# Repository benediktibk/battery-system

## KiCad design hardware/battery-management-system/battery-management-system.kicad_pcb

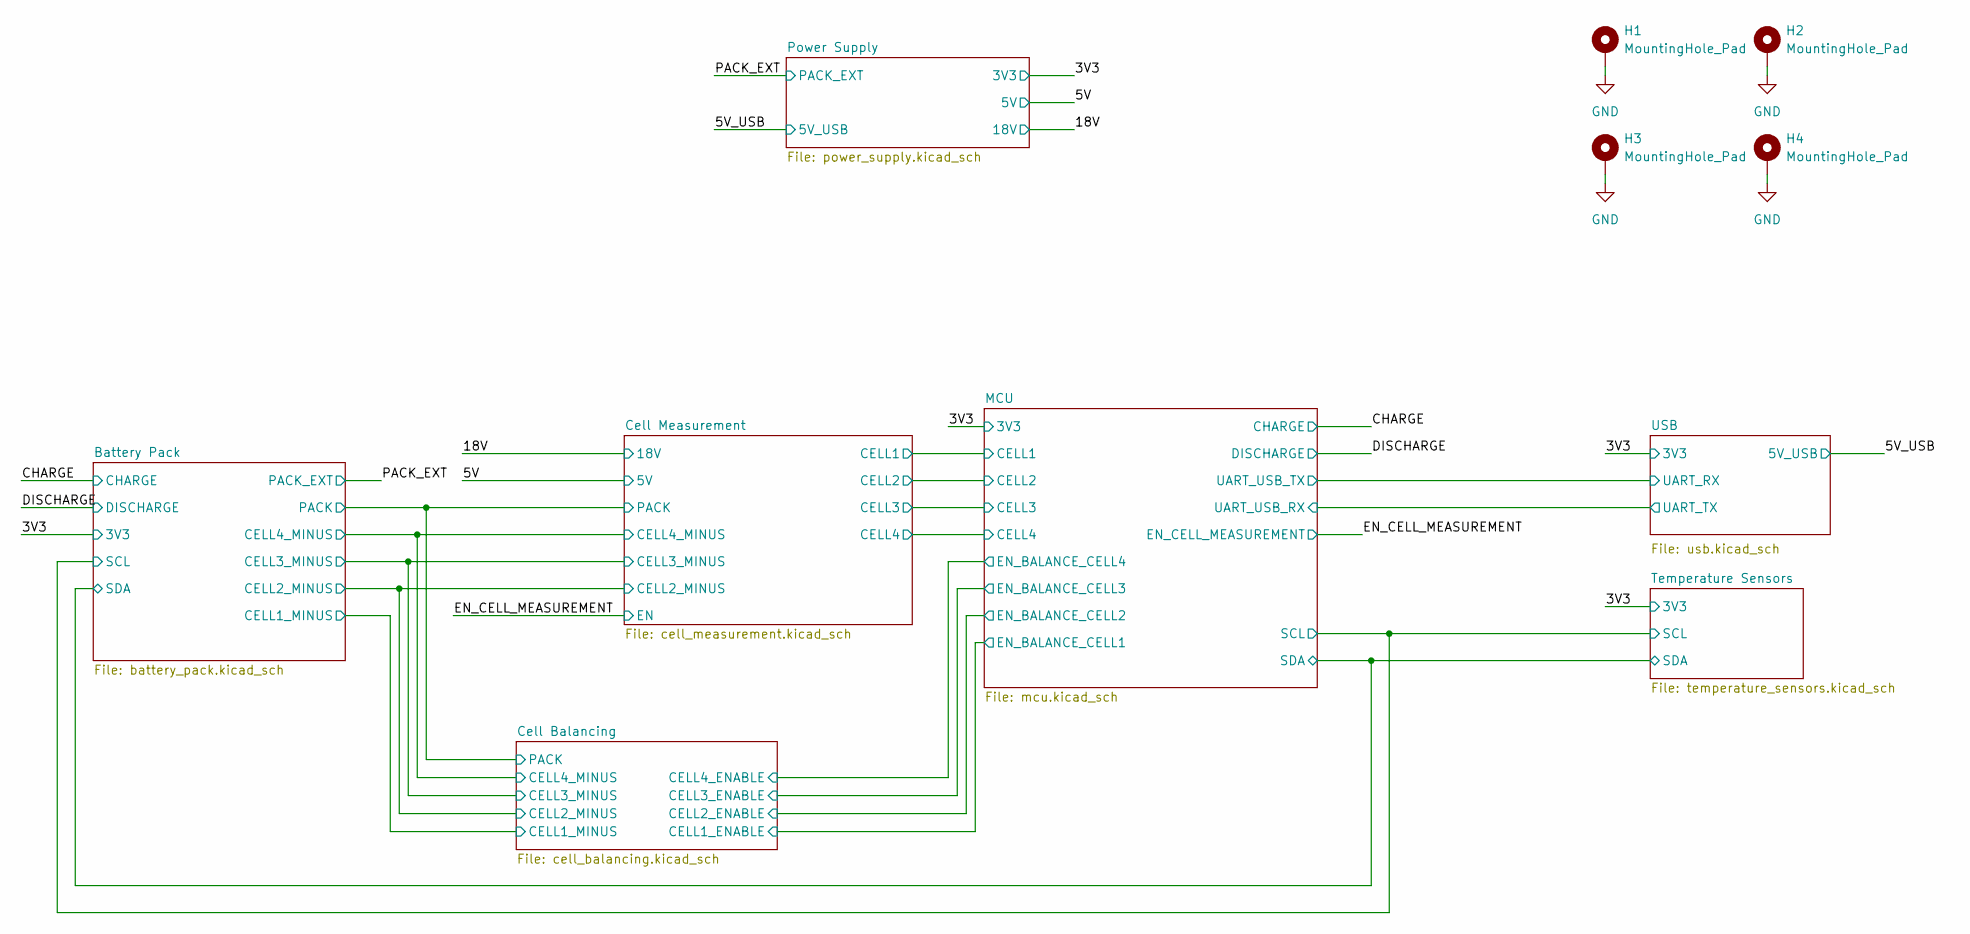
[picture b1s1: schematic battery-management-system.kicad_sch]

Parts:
H1, H2, H3, H4: MountingHole_Pad; MountingHole_6.4mm_M6_Pad_TopBottom

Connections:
GND: H1.1, H2.1, H3.1, H4.1; also elsewhere on the board

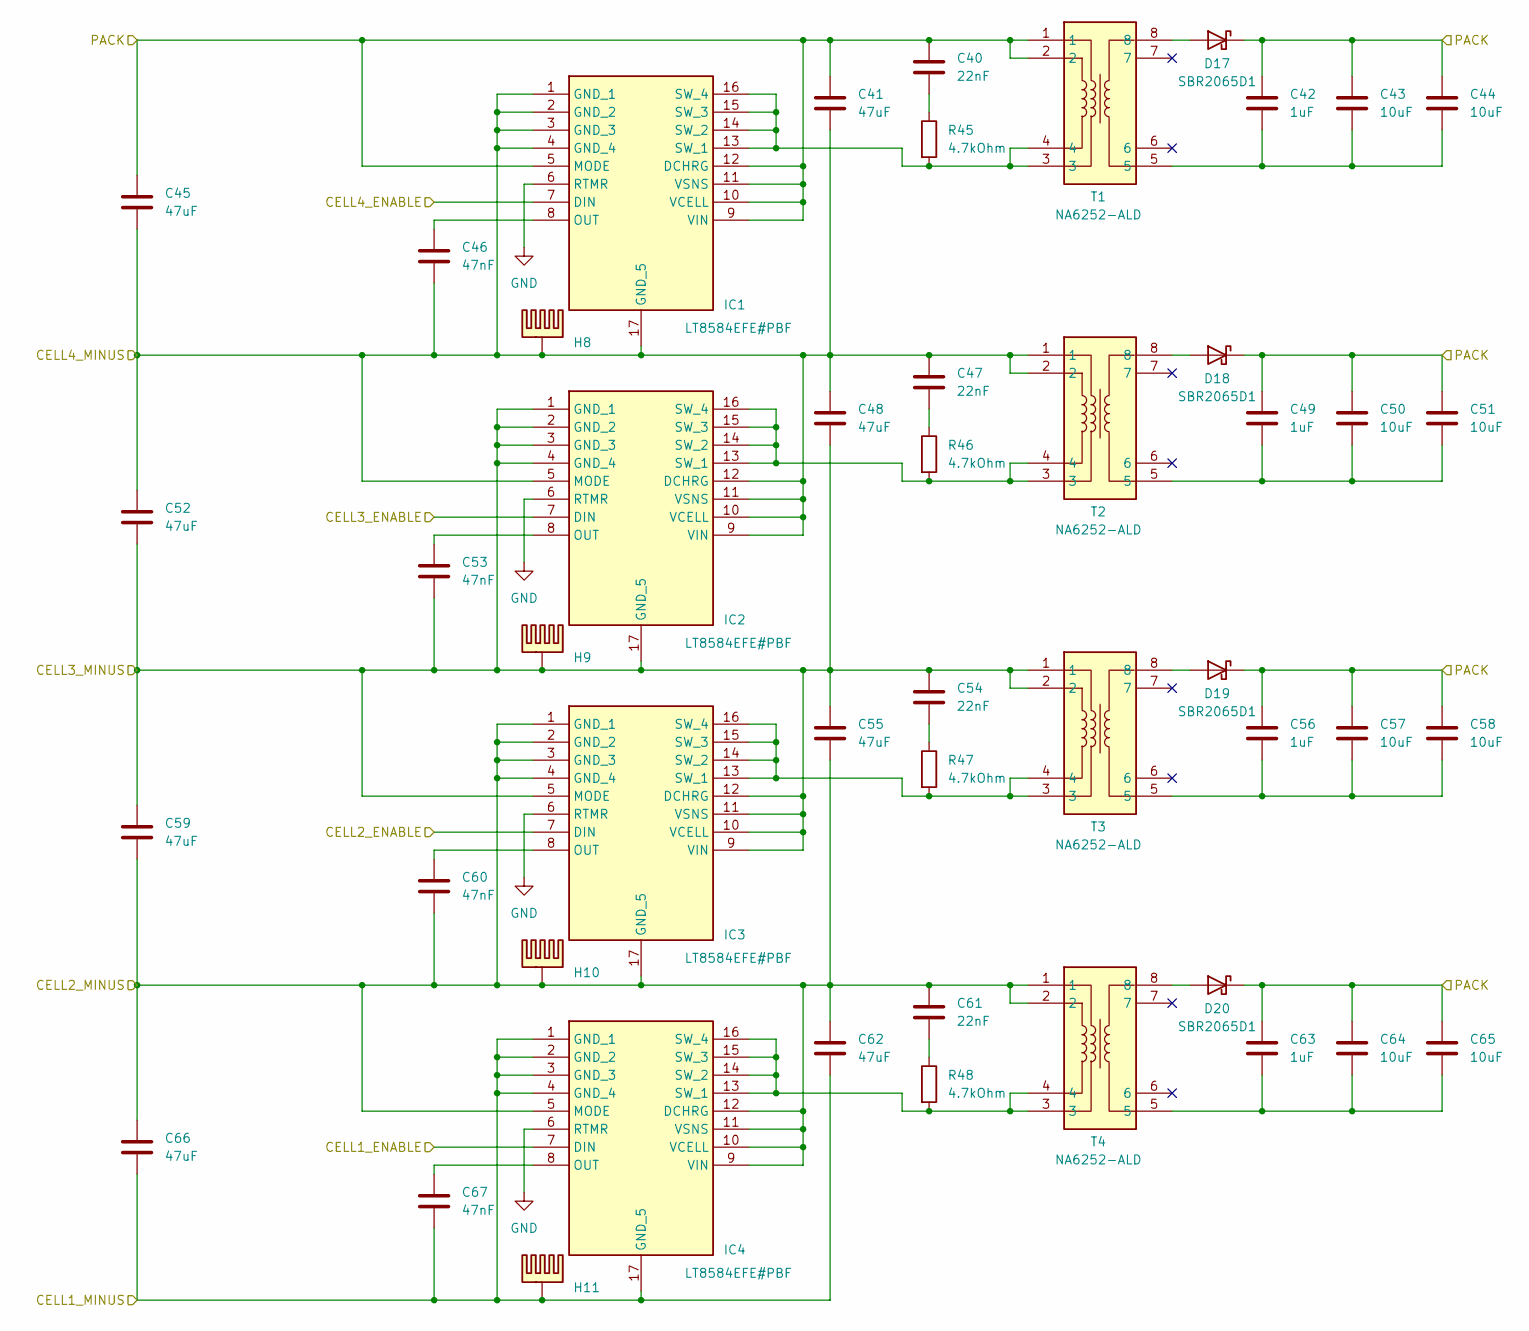
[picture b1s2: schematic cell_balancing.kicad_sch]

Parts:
C40, C47, C54, C61: 22nF; C_0603_1608Metric_Pad1.08x0.95mm_HandSolder; Mouser Part Number 80-C0603C223K4R
C41, C45, C48, C52, C55, C59, C62, C66: 47uF; C_1206_3216Metric_Pad1.33x1.80mm_HandSolder; Mouser Part Number 810-C3216X5R1E476M
C42, C49, C56, C63: 1uF; C_0603_1608Metric_Pad1.08x0.95mm_HandSolder; Mouser Part Number 963-UMK107BJ105KA-T
C43, C44, C50, C51, C57, C58, C64, C65: 10uF; C_1210_3225Metric_Pad1.33x2.70mm_HandSolder; Mouser Part Number 187-CL31A106MBHNNNE
C46, C53, C60, C67: 47nF; C_0603_1608Metric_Pad1.08x0.95mm_HandSolder; Mouser Part Number 80-C0603C473K4RACLR
D17, D18, D19, D20: SBR2065D1; Mouser Part Number 621-SBR2065D1-13
H8, H9, H10, H11: heatsink_18x18; Mouser Part Number 490-HSB06-181810; Mouser order number 490-HSB06-181810
IC1, IC2, IC3, IC4: LT8584EFE#PBF; SOP65P640X110-17N; Mouser Part Number 584-LT8584EFE#PBF; Mouser order number 584-LT8584EFE#PBF
R45, R46, R47, R48: 4.7kOhm; R_0603_1608Metric_Pad0.98x0.95mm_HandSolder; Mouser Part Number 652-CR0603FX-4701ELF
T1, T2, T3, T4: NA6252-ALD; SOP250P1524X1143-8N; Mouser Part Number 994-NA6252-ALD; Mouser order number 994-NA6252-ALD

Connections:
/Battery Pack/CELL1_MINUS: C62.2, C66.2, C67.2, H11.PAD, IC4.1 (GND_1), IC4.2 (GND_2), IC4.3 (GND_3), IC4.4 (GND_4), IC4.17 (GND_5); also elsewhere on the board
/Battery Pack/CELL2_MINUS: C55.2, C59.2, C60.2, C61.1, C62.1, C66.1, H10.PAD, IC3.1 (GND_1), IC3.2 (GND_2), IC3.3 (GND_3), IC3.4 (GND_4), IC3.17 (GND_5), IC4.5 (MODE), IC4.9 (VIN), IC4.10 (VCELL), IC4.11 (VSNS), IC4.12 (DCHRG), T4.1, T4.2; also elsewhere on the board
/Battery Pack/CELL3_MINUS: C48.2, C52.2, C53.2, C54.1, C55.1, C59.1, H9.PAD, IC2.1 (GND_1), IC2.2 (GND_2), IC2.3 (GND_3), IC2.4 (GND_4), IC2.17 (GND_5), IC3.5 (MODE), IC3.9 (VIN), IC3.10 (VCELL), IC3.11 (VSNS), IC3.12 (DCHRG), T3.1, T3.2; also elsewhere on the board
/Battery Pack/CELL4_MINUS: C41.2, C45.2, C46.2, C47.1, C48.1, C52.1, H8.PAD, IC1.1 (GND_1), IC1.2 (GND_2), IC1.3 (GND_3), IC1.4 (GND_4), IC1.17 (GND_5), IC2.5 (MODE), IC2.9 (VIN), IC2.10 (VCELL), IC2.11 (VSNS), IC2.12 (DCHRG), T2.1, T2.2; also elsewhere on the board
/Battery Pack/PACK: C40.1, C41.1, C42.1, C43.1, C44.1, C45.1, C49.1, C50.1, C51.1, C56.1, C57.1, C58.1, C63.1, C64.1, C65.1, D17.2 (K), D18.2 (K), D19.2 (K), D20.2 (K), IC1.5 (MODE), IC1.9 (VIN), IC1.10 (VCELL), IC1.11 (VSNS), IC1.12 (DCHRG), T1.1, T1.2; also elsewhere on the board
/Cell Balancing/CELL1_ENABLE: IC4.7 (DIN); also elsewhere on the board
/Cell Balancing/CELL2_ENABLE: IC3.7 (DIN); also elsewhere on the board
/Cell Balancing/CELL3_ENABLE: IC2.7 (DIN); also elsewhere on the board
/Cell Balancing/CELL4_ENABLE: IC1.7 (DIN); also elsewhere on the board
GND: IC1.6 (RTMR), IC2.6 (RTMR), IC3.6 (RTMR), IC4.6 (RTMR); also elsewhere on the board
unnamed: C40.2, R45.1
unnamed: C42.2, C43.2, C44.2, T1.5
unnamed: C47.2, R46.1
unnamed: C49.2, C50.2, C51.2, T2.5
unnamed: C54.2, R47.1
unnamed: C56.2, C57.2, C58.2, T3.5
unnamed: C61.2, R48.1
unnamed: C63.2, C64.2, C65.2, T4.5
unnamed: D17.1 (A), T1.8
unnamed: D18.1 (A), T2.8
unnamed: D19.1 (A), T3.8
unnamed: D20.1 (A), T4.8
unnamed: C46.1, IC1.8 (OUT)
unnamed: IC1.13 (SW_1), IC1.14 (SW_2), IC1.15 (SW_3), IC1.16 (SW_4), R45.2, T1.3, T1.4
unnamed: C53.1, IC2.8 (OUT)
unnamed: IC2.13 (SW_1), IC2.14 (SW_2), IC2.15 (SW_3), IC2.16 (SW_4), R46.2, T2.3, T2.4
unnamed: C60.1, IC3.8 (OUT)
unnamed: IC3.13 (SW_1), IC3.14 (SW_2), IC3.15 (SW_3), IC3.16 (SW_4), R47.2, T3.3, T3.4
unnamed: C67.1, IC4.8 (OUT)
unnamed: IC4.13 (SW_1), IC4.14 (SW_2), IC4.15 (SW_3), IC4.16 (SW_4), R48.2, T4.3, T4.4

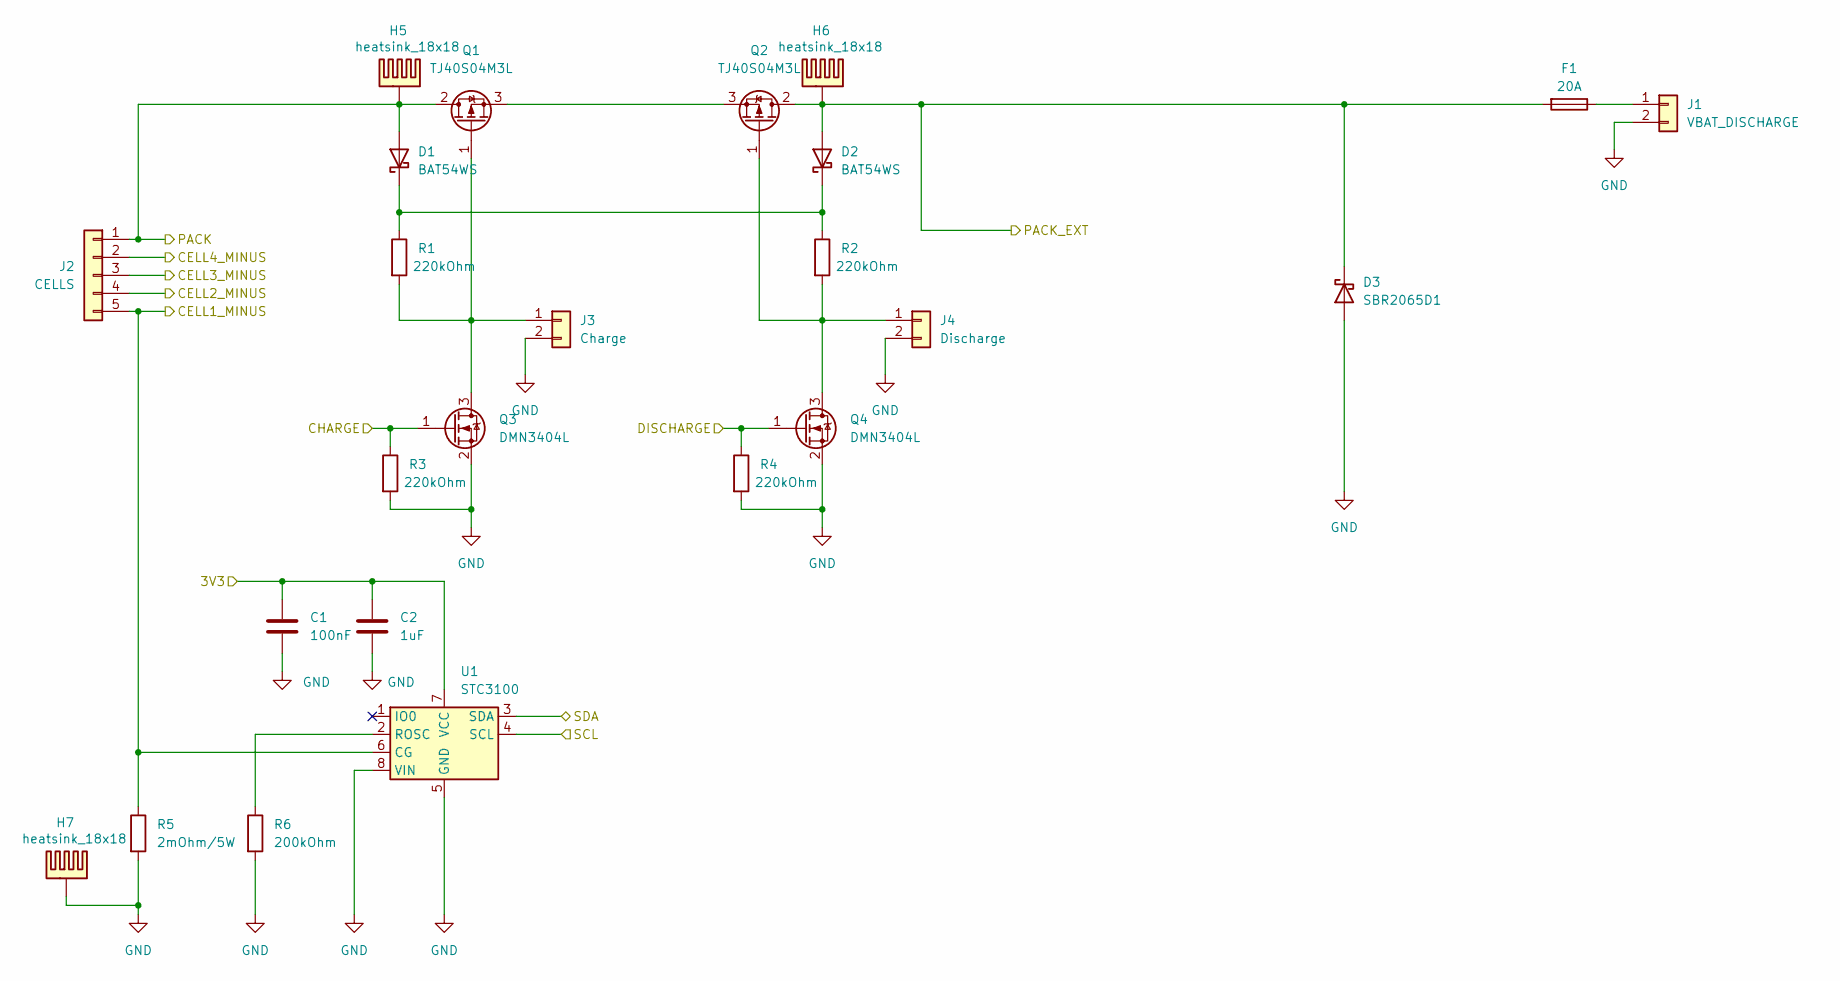
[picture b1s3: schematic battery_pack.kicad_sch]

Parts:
C1: 100nF; C_0603_1608Metric_Pad1.08x0.95mm_HandSolder; Mouser Part Number 581-KGM15BR71H104KM
C2: 1uF; C_0603_1608Metric_Pad1.08x0.95mm_HandSolder; Mouser Part Number 963-UMK107BJ105KA-T
D1, D2: BAT54WS; D_SOD-323; Mouser Part Number 637-BAT54WS
D3: SBR2065D1; Mouser Part Number 621-SBR2065D1-13
F1: 20A; KEYSTONE_blade_fus_holder
H5, H6, H7: heatsink_18x18; Mouser Part Number 490-HSB06-181810; Mouser order number 490-HSB06-181810
J1: VBAT_DISCHARGE; rspro_header_2pin_5_08mm
J2: CELLS; rspro_header_5pin_5_08mm
J3: Charge; PinHeader_1x02_P2.54mm_Vertical
J4: Discharge; PinHeader_1x02_P2.54mm_Vertical
Q1, Q2: TJ40S04M3L; TO-252-2; Mouser Part Number 757-TJ40S04M3LT6L1NQ
Q3, Q4: DMN3404L; SOT-23; Mouser Part Number 621-DMN3404L-7
R1, R2, R3, R4: 220kOhm; R_0603_1608Metric_Pad0.98x0.95mm_HandSolder; Mouser Part Number 71-CRCW0603-220K-E3
R5: 2mOhm/5W; R_2512_6332Metric_Pad1.40x3.35mm_HandSolder; Mouser Part Number 660-TLR3APSDTE2L00F7
R6: 200kOhm; R_0603_1608Metric_Pad0.98x0.95mm_HandSolder; Mouser Part Number 667-ERA-3AEB204V
U1: STC3100; MSOP-8_3x3mm_P0.65mm; Mouser Part Number 511-STC3100IST

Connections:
/3V3: C1.1, C2.1, U1.7 (VCC); also elsewhere on the board
/Battery Pack/CELL1_MINUS: J2.5, R5.1, U1.6 (CG); also elsewhere on the board
/Battery Pack/CELL2_MINUS: J2.4; also elsewhere on the board
/Battery Pack/CELL3_MINUS: J2.3; also elsewhere on the board
/Battery Pack/CELL4_MINUS: J2.2; also elsewhere on the board
/Battery Pack/PACK: D1.2 (A), H5.PAD, J2.1, Q1.2 (D); also elsewhere on the board
/CHARGE: Q3.1 (G), R3.1; also elsewhere on the board
/DISCHARGE: Q4.1 (G), R4.1; also elsewhere on the board
/MCU/SCL: U1.4 (SCL); also elsewhere on the board
/MCU/SDA: U1.3 (SDA); also elsewhere on the board
/PACK_EXT: D2.2 (A), D3.2 (K), F1.2, H6.PAD, Q2.2 (D); also elsewhere on the board
GND: C1.2, C2.2, D3.1 (A), H7.PAD, J1.2, J3.2, J4.2, Q3.2 (S), Q4.2 (S), R3.2, R4.2, R5.2, R6.2, U1.5 (GND), U1.8 (VIN); also elsewhere on the board
unnamed: D1.1 (K), D2.1 (K), R1.1, R2.1
unnamed: F1.1, J1.1
unnamed: J3.1, Q1.1 (G), Q3.3 (D), R1.2
unnamed: J4.1, Q2.1 (G), Q4.3 (D), R2.2
unnamed: Q1.3 (S), Q2.3 (S)
unnamed: R6.1, U1.2 (ROSC)

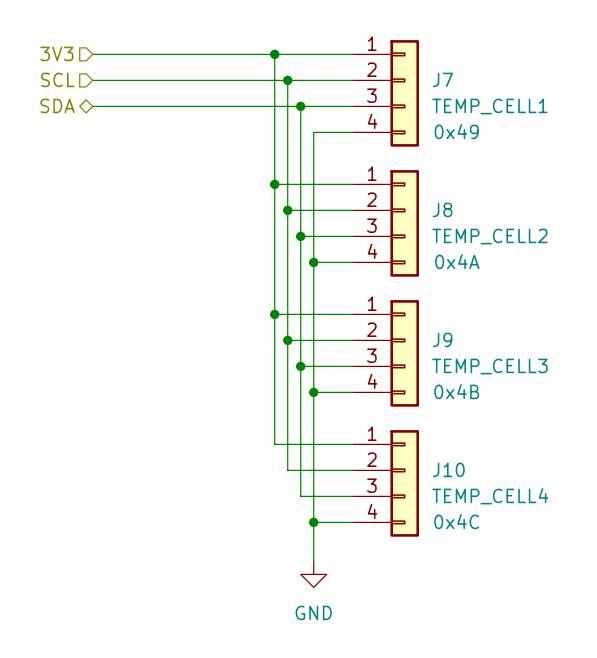
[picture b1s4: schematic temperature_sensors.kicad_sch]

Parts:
J7: TEMP_CELL1; rspro_header_4pin_3_5mm
J8: TEMP_CELL2; rspro_header_4pin_3_5mm
J9: TEMP_CELL3; rspro_header_4pin_3_5mm
J10: TEMP_CELL4; rspro_header_4pin_3_5mm

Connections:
/3V3: J7.1, J8.1, J9.1, J10.1; also elsewhere on the board
/MCU/SCL: J7.2, J8.2, J9.2, J10.2; also elsewhere on the board
/MCU/SDA: J7.3, J8.3, J9.3, J10.3; also elsewhere on the board
GND: J7.4, J8.4, J9.4, J10.4; also elsewhere on the board

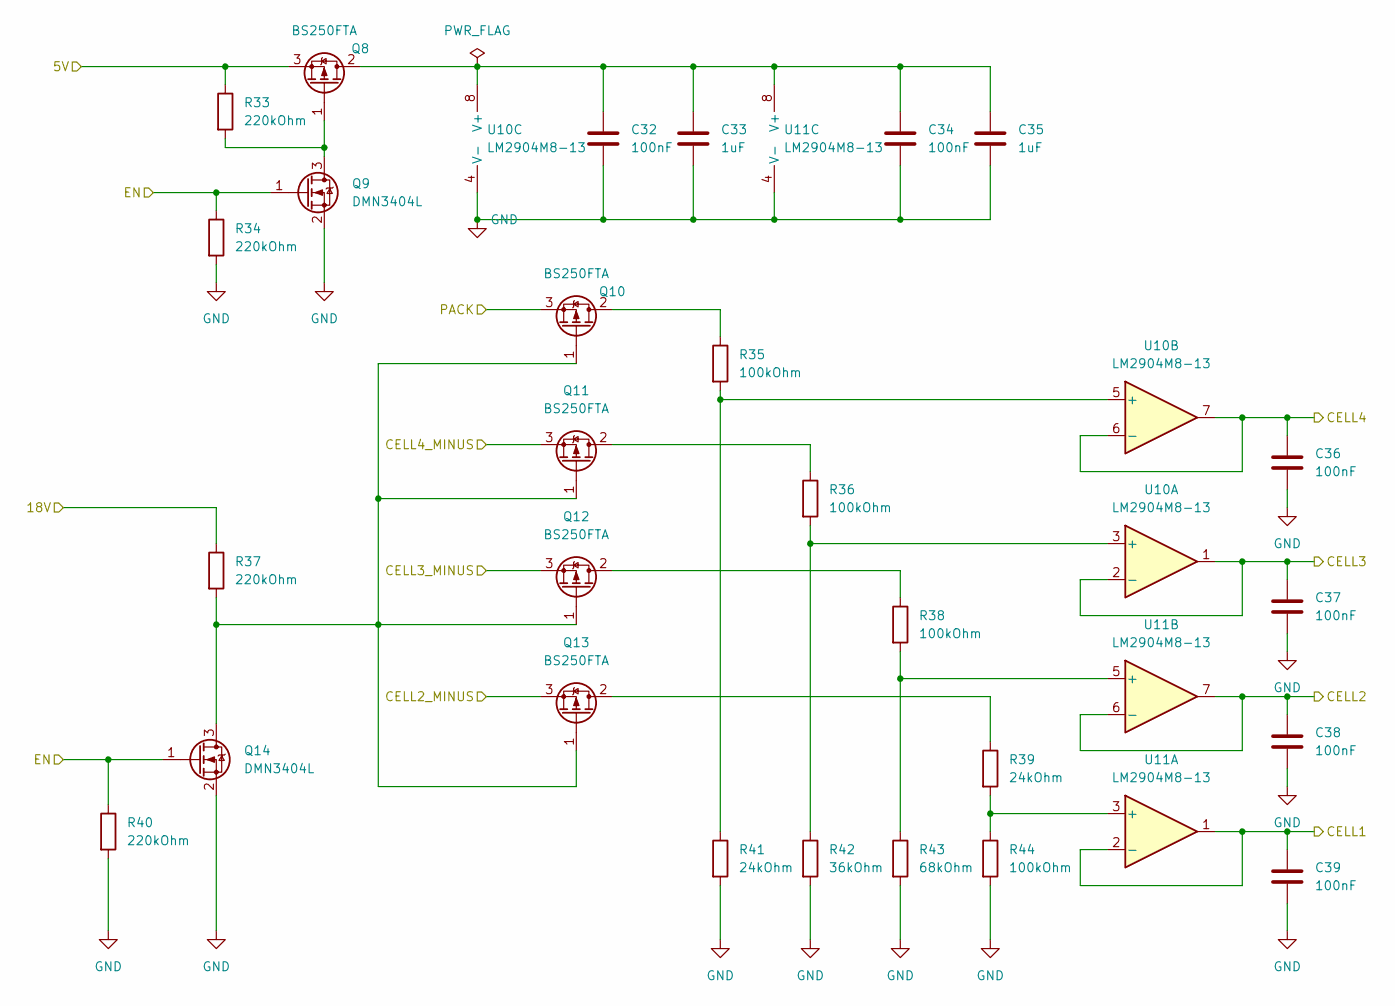
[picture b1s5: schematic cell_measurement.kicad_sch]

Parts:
C32, C34, C36, C37, C38, C39: 100nF; C_0603_1608Metric_Pad1.08x0.95mm_HandSolder; Mouser Part Number 581-KGM15BR71H104KM
C33, C35: 1uF; C_0603_1608Metric_Pad1.08x0.95mm_HandSolder; Mouser Part Number 963-UMK107BJ105KA-T
Q8, Q10, Q11, Q12, Q13: BS250FTA; SOT-23; Mouser Part Number 522-BS250FTA
Q9, Q14: DMN3404L; SOT-23; Mouser Part Number 621-DMN3404L-7
R33, R34, R37, R40: 220kOhm; R_0603_1608Metric_Pad0.98x0.95mm_HandSolder; Mouser Part Number 71-CRCW0603-220K-E3
R35, R36, R38, R44: 100kOhm; R_0603_1608Metric_Pad0.98x0.95mm_HandSolder; Mouser Part Number 603-RT0603FRE13100KL
R39, R41: 24kOhm; R_0603_1608Metric_Pad0.98x0.95mm_HandSolder; Mouser Part Number 71-CRCW060324K0FKEAC
R42: 36kOhm; R_0603_1608Metric_Pad0.98x0.95mm_HandSolder; Mouser Part Number 652-CR0603FX-3602ELF
R43: 68kOhm; R_0603_1608Metric_Pad0.98x0.95mm_HandSolder; Mouser Part Number 603-RT0603FRE0768KL
U10, U11: LM2904M8-13; MSOP-8_3x3mm_P0.65mm; Mouser Part Number 621-LM2904M8-13

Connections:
/5V: Q8.3 (S), R33.1; also elsewhere on the board
/18V: R37.1; also elsewhere on the board
/Battery Pack/CELL2_MINUS: Q13.3 (S); also elsewhere on the board
/Battery Pack/CELL3_MINUS: Q12.3 (S); also elsewhere on the board
/Battery Pack/CELL4_MINUS: Q11.3 (S); also elsewhere on the board
/Battery Pack/PACK: Q10.3 (S); also elsewhere on the board
/Cell Measurement/CELL1: C39.1, U11.1, U11.2 (-); also elsewhere on the board
/Cell Measurement/CELL2: C38.1, U11.6 (-), U11.7; also elsewhere on the board
/Cell Measurement/CELL3: C37.1, U10.1, U10.2 (-); also elsewhere on the board
/Cell Measurement/CELL4: C36.1, U10.6 (-), U10.7; also elsewhere on the board
/EN_CELL_MEASUREMENT: Q9.1 (G), Q14.1 (G), R34.1, R40.1; also elsewhere on the board
GND: C32.2, C33.2, C34.2, C35.2, C36.2, C37.2, C38.2, C39.2, Q9.2 (S), Q14.2 (S), R34.2, R40.2, R41.2, R42.2, R43.2, R44.2, U10.4 (V-), U11.4 (V-); also elsewhere on the board
unnamed: C32.1, C33.1, C34.1, C35.1, Q8.2 (D), U10.8 (V+), U11.8 (V+)
unnamed: Q8.1 (G), Q9.3 (D), R33.2
unnamed: Q10.2 (D), R35.1
unnamed: Q10.1 (G), Q11.1 (G), Q12.1 (G), Q13.1 (G), Q14.3 (D), R37.2
unnamed: Q11.2 (D), R36.1
unnamed: Q12.2 (D), R38.1
unnamed: Q13.2 (D), R39.1
unnamed: R36.2, R42.1, U10.3 (+)
unnamed: R35.2, R41.1, U10.5 (+)
unnamed: R39.2, R44.1, U11.3 (+)
unnamed: R38.2, R43.1, U11.5 (+)

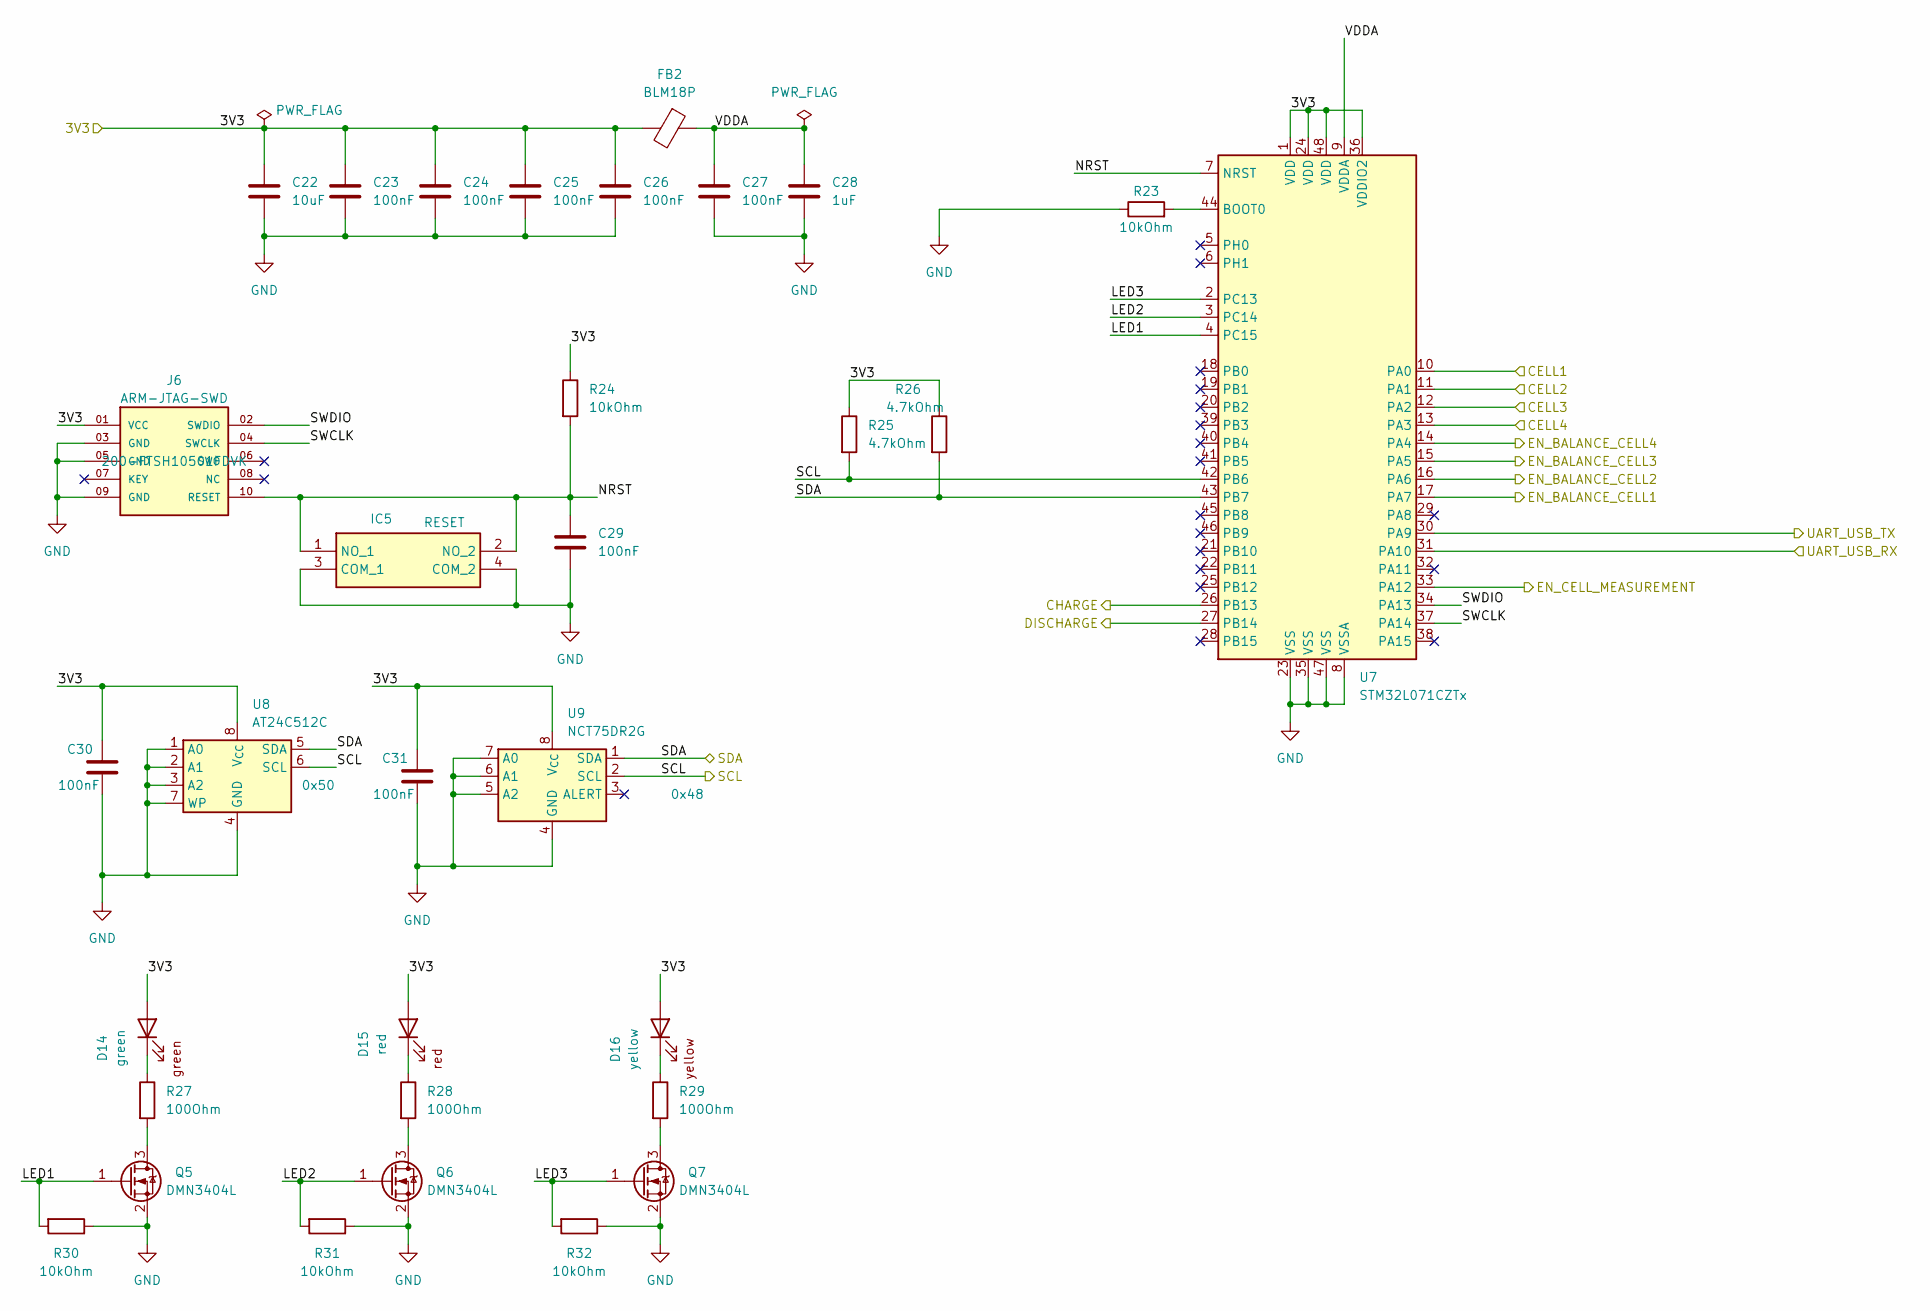
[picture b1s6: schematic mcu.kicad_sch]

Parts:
C22: 10uF; C_1210_3225Metric_Pad1.33x2.70mm_HandSolder; Mouser Part Number 187-CL31A106MBHNNNE
C23, C24, C25, C26, C27, C29, C30, C31: 100nF; C_0603_1608Metric_Pad1.08x0.95mm_HandSolder; Mouser Part Number 581-KGM15BR71H104KM
C28: 1uF; C_0603_1608Metric_Pad1.08x0.95mm_HandSolder; Mouser Part Number 963-UMK107BJ105KA-T
D14: green; D_0603_1608Metric_Pad1.05x0.95mm_HandSolder; Mouser Part Number 604-AP1608SGC
D15: red; D_0603_1608Metric_Pad1.05x0.95mm_HandSolder; Mouser Part Number 859-LTST-C190KDKT10A
D16: yellow; D_0603_1608Metric_Pad1.05x0.95mm_HandSolder; Mouser Part Number 604-APG1608SYKC/T
FB2: BLM18P; R_0603_1608Metric_Pad0.98x0.95mm_HandSolder; Mouser Part Number 81-BLM11P300S
IC5: RESET; TS026650BK100SCRD; Mouser Part Number 179-TS026650BK100SCR
J6: ARM-JTAG-SWD; SAMTEC_FTSH-105-01-F-DV-P-TR; Mouser Part Number 200-FTSH10501FDVK
Q5, Q6, Q7: DMN3404L; SOT-23; Mouser Part Number 621-DMN3404L-7
R23, R24, R30, R31, R32: 10kOhm; R_0603_1608Metric_Pad0.98x0.95mm_HandSolder; Mouser Part Number 652-CR0603FX-1002ELF
R25, R26: 4.7kOhm; R_0603_1608Metric_Pad0.98x0.95mm_HandSolder; Mouser Part Number 652-CR0603FX-4701ELF
R27, R28, R29: 100Ohm; R_0603_1608Metric_Pad0.98x0.95mm_HandSolder; Mouser Part Number 279-CRGH0603F100R
U7: STM32L071CZTx; LQFP-48_7x7mm_P0.5mm; Mouser Part Number 511-STM32L071CZT6
U8: AT24C512C; SOIC-8_3.9x4.9mm_P1.27mm; Mouser Part Number 556-AT24C512C-SSHM-T
U9: NCT75DR2G; SOIC-8_3.9x4.9mm_P1.27mm; Mouser Part Number 863-NCT75DR2G

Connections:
/3V3: C22.1, C23.1, C24.1, C25.1, C26.1, C30.1, C31.1, D14.2 (A), D15.2 (A), D16.2 (A), FB2.2, J6.01 (VCC), R24.1, R25.1, R26.1, U7.1 (VDD), U7.24 (VDD), U7.36 (VDDIO2), U7.48 (VDD), U8.8 (V_{CC}), U9.8 (V_{CC}); also elsewhere on the board
/CHARGE: U7.26 (PB13); also elsewhere on the board
/Cell Balancing/CELL1_ENABLE: U7.17 (PA7); also elsewhere on the board
/Cell Balancing/CELL2_ENABLE: U7.16 (PA6); also elsewhere on the board
/Cell Balancing/CELL3_ENABLE: U7.15 (PA5); also elsewhere on the board
/Cell Balancing/CELL4_ENABLE: U7.14 (PA4); also elsewhere on the board
/Cell Measurement/CELL1: U7.10 (PA0); also elsewhere on the board
/Cell Measurement/CELL2: U7.11 (PA1); also elsewhere on the board
/Cell Measurement/CELL3: U7.12 (PA2); also elsewhere on the board
/Cell Measurement/CELL4: U7.13 (PA3); also elsewhere on the board
/DISCHARGE: U7.27 (PB14); also elsewhere on the board
/EN_CELL_MEASUREMENT: U7.33 (PA12); also elsewhere on the board
/MCU/LED1: Q5.1 (G), R30.2, U7.4 (PC15)
/MCU/LED2: Q6.1 (G), R31.2, U7.3 (PC14)
/MCU/LED3: Q7.1 (G), R32.2, U7.2 (PC13)
/MCU/NRST: C29.1, IC5.1 (NO_1), IC5.2 (NO_2), J6.10 (RESET), R24.2, U7.7 (NRST)
/MCU/SCL: R25.2, U7.42 (PB6), U8.6 (SCL), U9.2 (SCL); also elsewhere on the board
/MCU/SDA: R26.2, U7.43 (PB7), U8.5 (SDA), U9.1 (SDA); also elsewhere on the board
/MCU/SWCLK: J6.04 (SWCLK), U7.37 (PA14)
/MCU/SWDIO: J6.02 (SWDIO), U7.34 (PA13)
/MCU/UART_USB_RX: U7.31 (PA10); also elsewhere on the board
/MCU/UART_USB_TX: U7.30 (PA9); also elsewhere on the board
/MCU/VDDA: C27.1, C28.1, FB2.1, U7.9 (VDDA)
GND: C22.2, C23.2, C24.2, C25.2, C26.2, C27.2, C28.2, C29.2, C30.2, C31.2, IC5.3 (COM_1), IC5.4 (COM_2), J6.03 (GND), J6.05 (GND), J6.09 (GND), Q5.2 (S), Q6.2 (S), Q7.2 (S), R23.1, R30.1, R31.1, R32.1, U7.8 (VSSA), U7.23 (VSS), U7.35 (VSS), U7.47 (VSS), U8.1 (A0), U8.2 (A1), U8.3 (A2), U8.4 (GND), U8.7 (WP), U9.4 (GND), U9.5 (A2), U9.6 (A1), U9.7 (A0); also elsewhere on the board
unnamed: D14.1 (K), R27.1
unnamed: D15.1 (K), R28.1
unnamed: D16.1 (K), R29.1
unnamed: Q5.3 (D), R27.2
unnamed: Q6.3 (D), R28.2
unnamed: Q7.3 (D), R29.2
unnamed: R23.2, U7.44 (BOOT0)

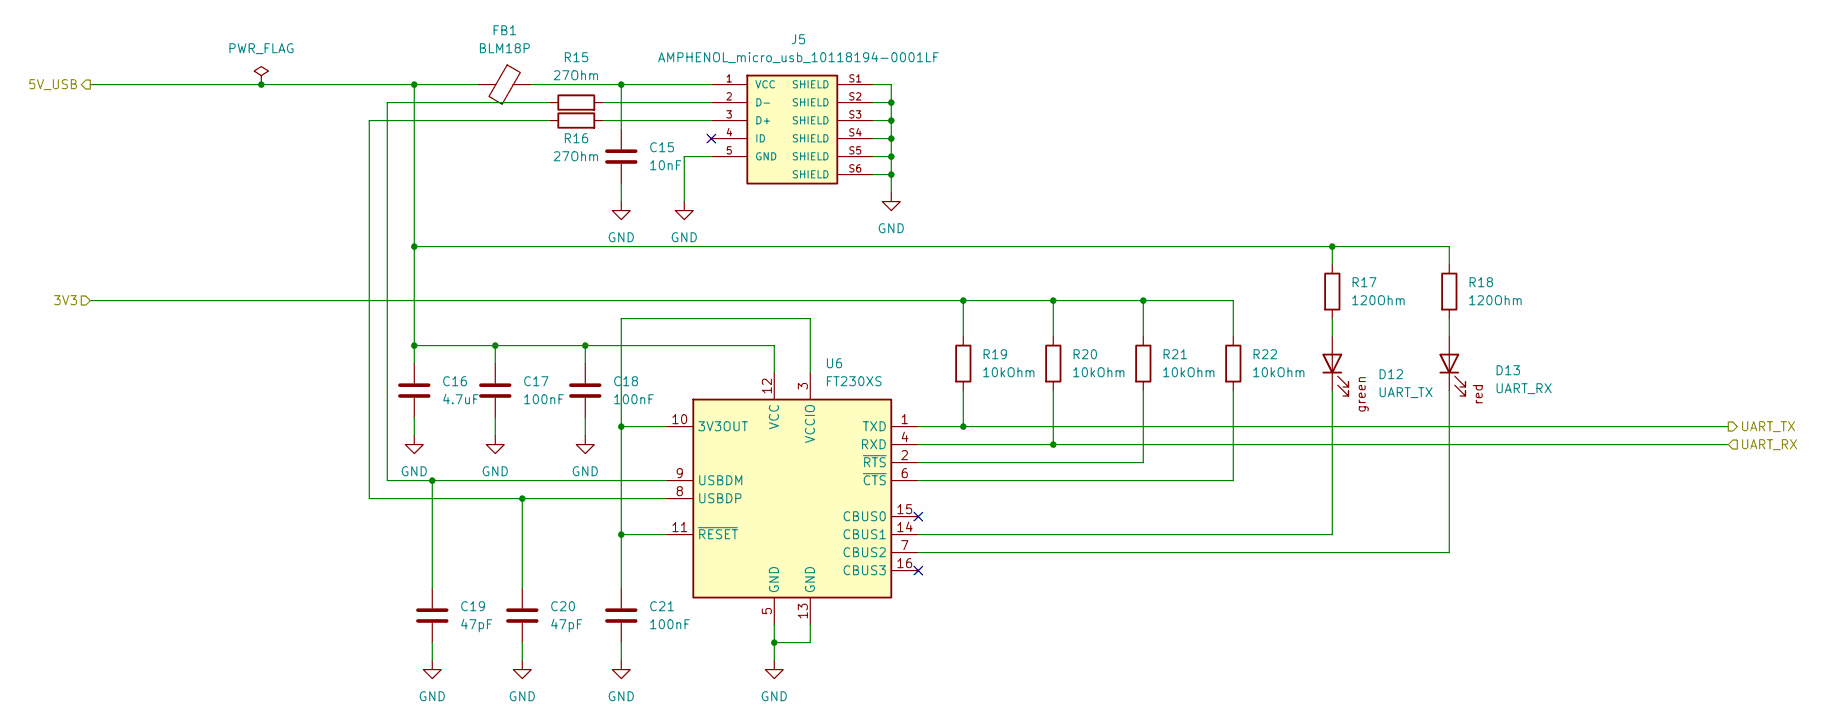
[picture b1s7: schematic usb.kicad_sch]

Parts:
C15: 10nF; C_0603_1608Metric_Pad1.08x0.95mm_HandSolder; Mouser Part Number 80-C0603C103M5R3121
C16: 4.7uF; C_0805_2012Metric_Pad1.18x1.45mm_HandSolder; Mouser Part Number 187-CL21A475KBQNNNE
C17, C18, C21: 100nF; C_0603_1608Metric_Pad1.08x0.95mm_HandSolder; Mouser Part Number 581-KGM15BR71H104KM
C19, C20: 47pF; C_0603_1608Metric_Pad1.08x0.95mm_HandSolder; Mouser Part Number 791-0603N470J101CT
D12: UART_TX; D_0603_1608Metric_Pad1.05x0.95mm_HandSolder; Mouser Part Number 604-AP1608SGC
D13: UART_RX; D_0603_1608Metric_Pad1.05x0.95mm_HandSolder; Mouser Part Number 859-LTST-C190KDKT10A
FB1: BLM18P; R_0603_1608Metric_Pad0.98x0.95mm_HandSolder; Mouser Part Number 81-BLM11P300S
J5: AMPHENOL_micro_usb_10118194-0001LF; AMPHENOL_10118194-0001LF; Mouser Part Number 649-10118194-0001LF
R15, R16: 27Ohm; R_0603_1608Metric_Pad0.98x0.95mm_HandSolder; Mouser Part Number 603-RC0603FR-0727RL
R17, R18: 120Ohm; R_0603_1608Metric_Pad0.98x0.95mm_HandSolder; Mouser Part Number 603-RC0603FR-07120RL
R19, R20, R21, R22: 10kOhm; R_0603_1608Metric_Pad0.98x0.95mm_HandSolder; Mouser Part Number 652-CR0603FX-1002ELF
U6: FT230XS; SSOP-16_3.9x4.9mm_P0.635mm; Mouser Part Number 895-FT230XS-R

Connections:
/3V3: R19.1, R20.1, R21.1, R22.1; also elsewhere on the board
/5V_USB: C16.1, C17.1, C18.1, FB1.2, R17.1, R18.1, U6.12 (VCC); also elsewhere on the board
/MCU/UART_USB_RX: R19.2, U6.1 (TXD); also elsewhere on the board
/MCU/UART_USB_TX: R20.2, U6.4 (RXD); also elsewhere on the board
GND: C15.2, C16.2, C17.2, C18.2, C19.2, C20.2, C21.2, J5.5 (GND), J5.S1 (SHIELD), J5.S2 (SHIELD), J5.S3 (SHIELD), J5.S4 (SHIELD), J5.S5 (SHIELD), J5.S6 (SHIELD), U6.5 (GND), U6.13 (GND); also elsewhere on the board
unnamed: D12.2 (A), R17.2
unnamed: D12.1 (K), U6.14 (CBUS1)
unnamed: D13.2 (A), R18.2
unnamed: D13.1 (K), U6.7 (CBUS2)
unnamed: J5.3 (D+), R16.2
unnamed: J5.2 (D-), R15.2
unnamed: C15.1, FB1.1, J5.1 (VCC)
unnamed: C21.1, U6.3 (VCCIO), U6.10 (3V3OUT), U6.11 (~RESET)
unnamed: C19.1, R15.1, U6.9 (USBDM)
unnamed: C20.1, R16.1, U6.8 (USBDP)
unnamed: R22.2, U6.6 (~CTS)
unnamed: R21.2, U6.2 (~RTS)
